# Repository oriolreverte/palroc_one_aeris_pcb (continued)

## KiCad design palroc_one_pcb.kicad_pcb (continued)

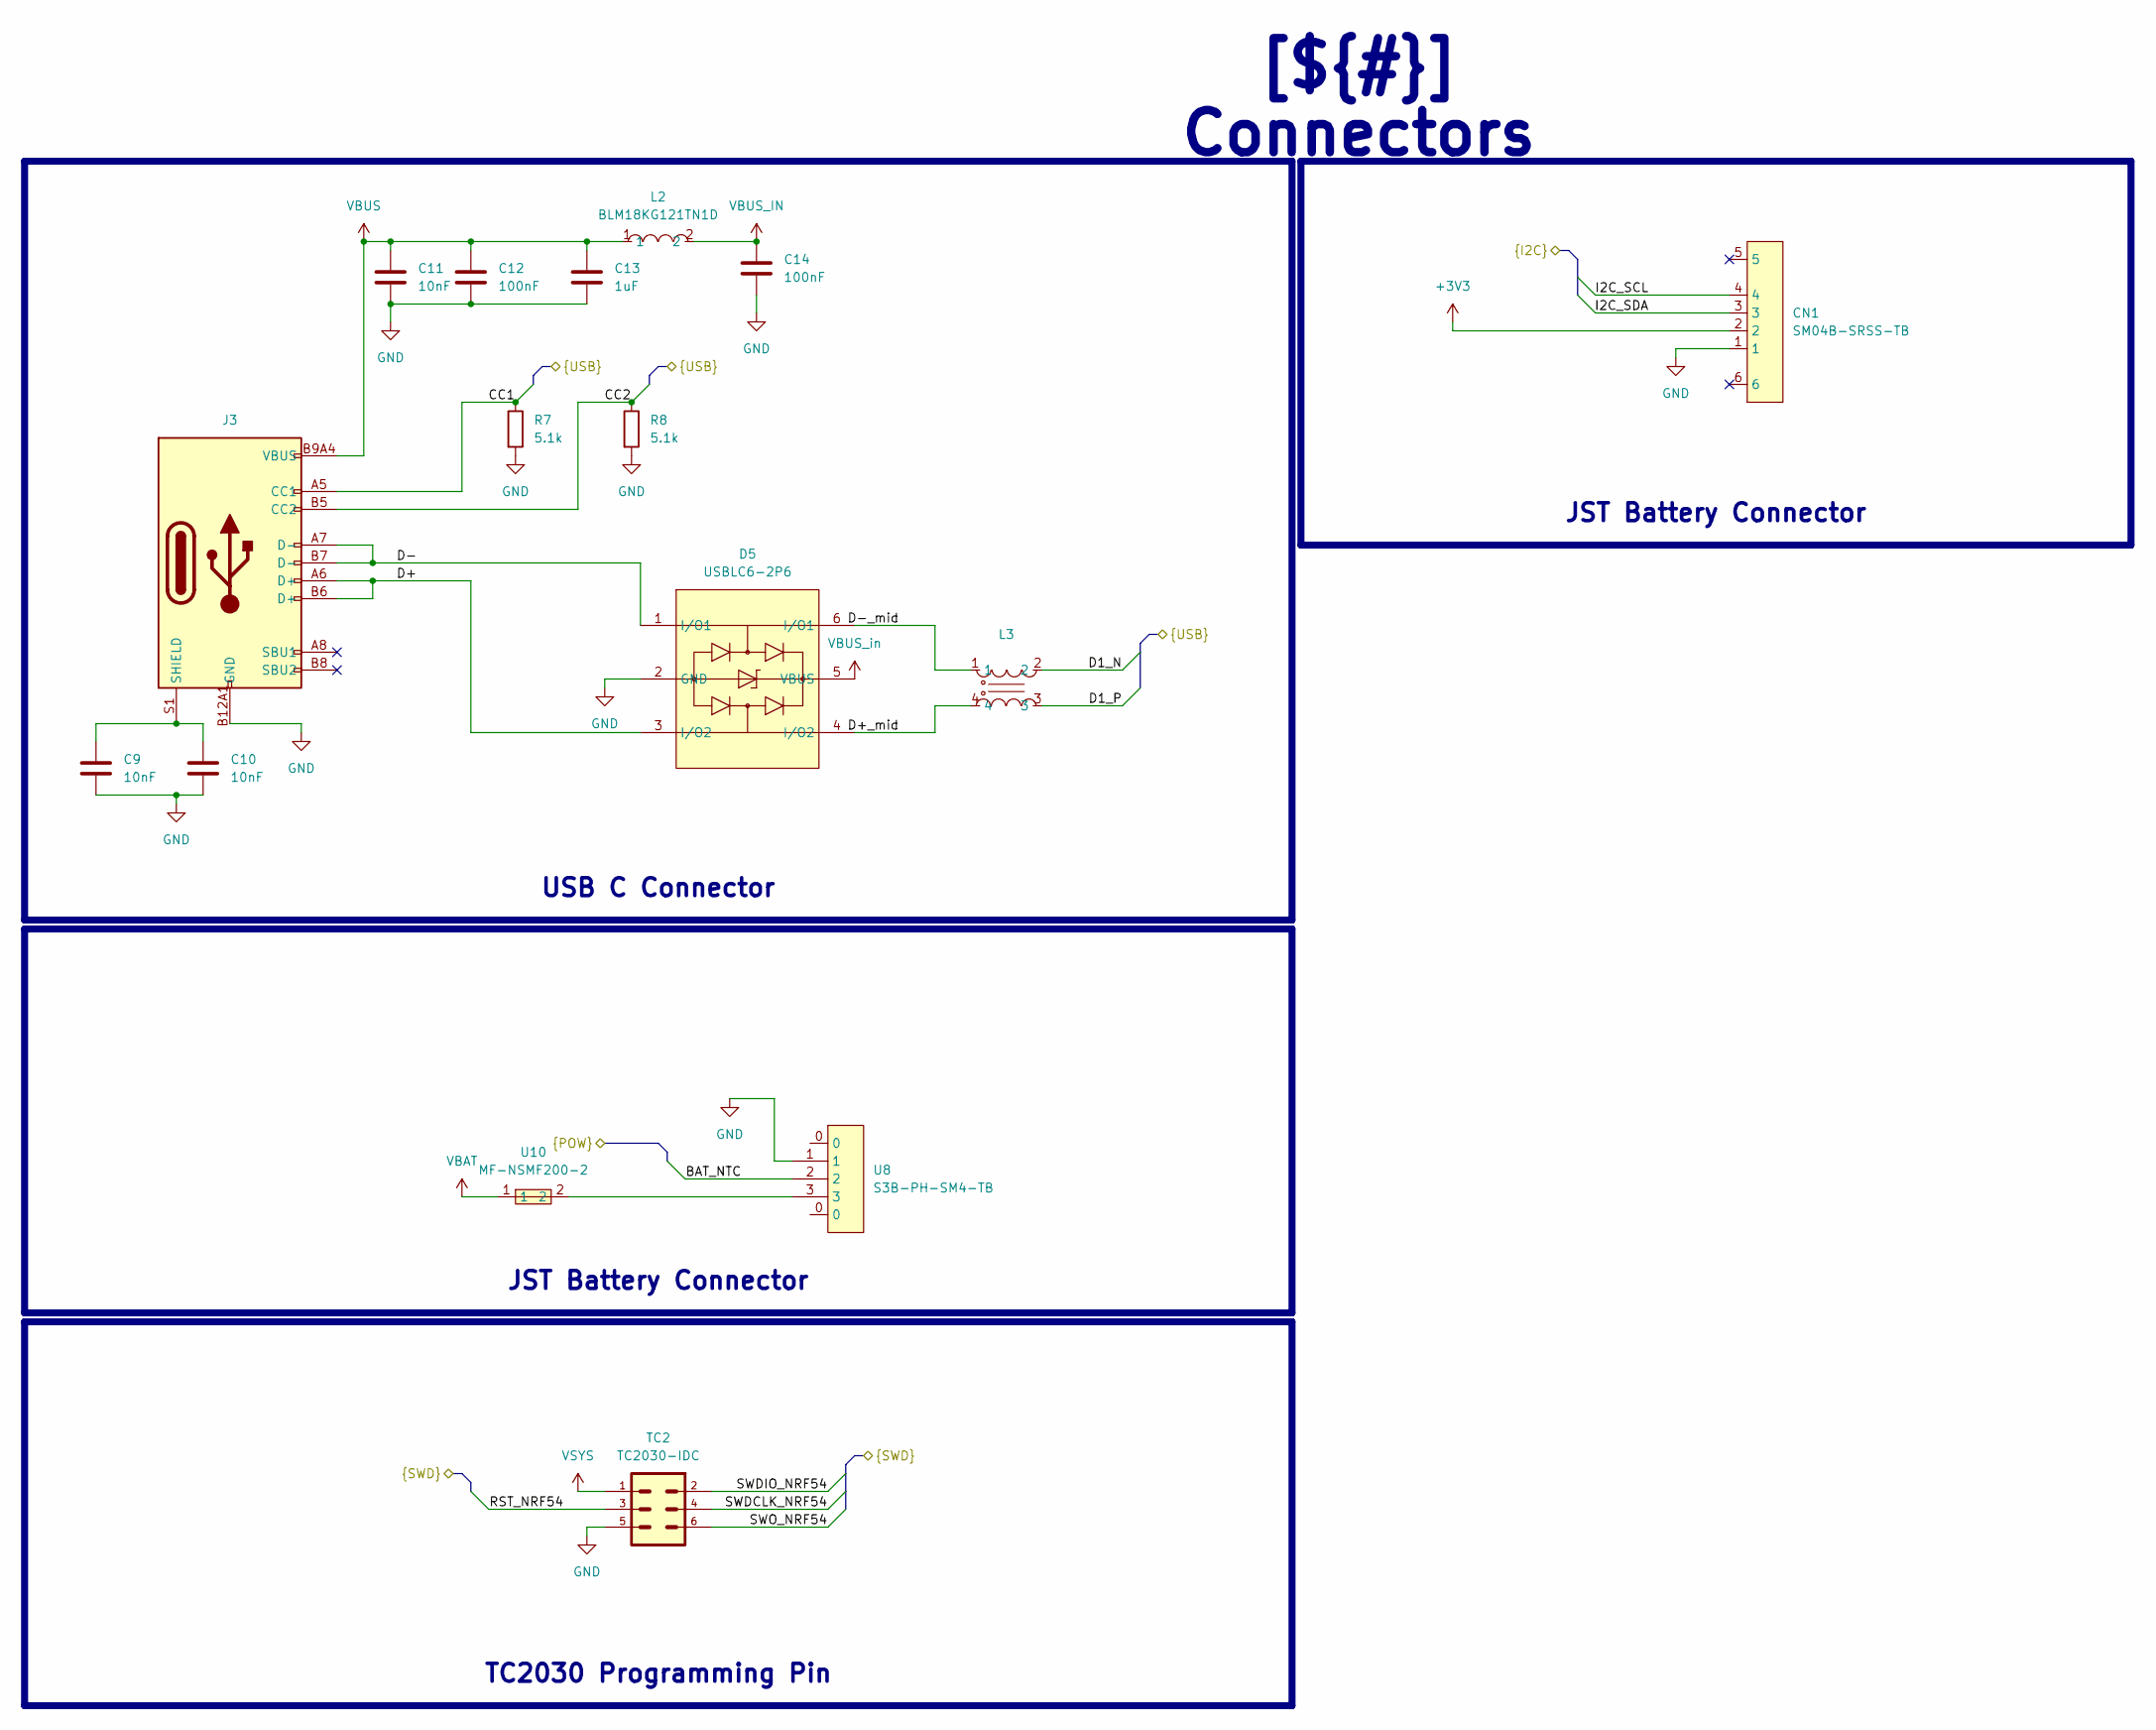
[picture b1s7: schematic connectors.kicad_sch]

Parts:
C9, C10, C11: 10nF; c_0402_nordic; LCSC C15195
C12, C14: 100nF; c_0402_nordic; LCSC C1525
C13: 1uF; c_0402_nordic; LCSC C52923
CN1: SM04B-SRSS-TB; CONN-SMD_4P-P1.00_SM04B-SRSS-TB-LF-SN; MPN SM04B-SRSS-TB(LF)(SN); LCSC Part C160404
D5: USBLC6-2P6; SOT-666-6_L1.6-W1.2-P0.50-LS1.6-BR; MPN USBLC6-2P6; LCSC Part C15999
J3: Connector, USB-TYPE-C-16P; TYPE-C-SMD_HX-TYPE-C-16PIN; LCSC C2927039
L2: BLM18KG121TN1D; L0603; MPN BLM18KG121TN1D; LCSC Part C85831
L3: DLM0NSN900HY2D; FILTER-SMD_4P-L0.9-W0.7-P0.50-BL-CW; MPN DLM0NSN900HY2D; LCSC Part C882594
R7, R8: 5.1k; r_0402_nordic; LCSC C25905
TC2: TC2030-IDC
U8: S3B-PH-SM4-TB; CONN-SMD_S3B-PH-SM4-TB-LF-SN; MPN S3B-PH-SM4-TB(LF)(SN); LCSC Part C265101
U10: MF-NSMF200-2; F1206; MPN MF-NSMF200-2; LCSC Part C89656

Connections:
+3V3: CN1.2; also elsewhere on the board
/Project Architecture/Connectors/BAT_NTC: U8.2; also elsewhere on the board
/Project Architecture/Connectors/CC1: J3.A5 (CC1), R7.1; also elsewhere on the board
/Project Architecture/Connectors/CC2: J3.B5 (CC2), R8.1; also elsewhere on the board
/Project Architecture/Connectors/D1_N: L3.2; also elsewhere on the board
/Project Architecture/Connectors/D1_P: L3.3; also elsewhere on the board
/Project Architecture/Connectors/D+: D5.3 (I/O2), J3.A6 (D+), J3.B6 (D+)
/Project Architecture/Connectors/D+_mid: D5.4 (I/O2), L3.4
/Project Architecture/Connectors/D-: D5.1 (I/O1), J3.A7 (D-), J3.B7 (D-)
/Project Architecture/Connectors/D-_mid: D5.6 (I/O1), L3.1
/Project Architecture/Connectors/I2C_SCL: CN1.4; also elsewhere on the board
/Project Architecture/Connectors/I2C_SDA: CN1.3; also elsewhere on the board
/Project Architecture/Connectors/RST_NRF54: TC2.3; also elsewhere on the board
/Project Architecture/Connectors/SWDCLK_NRF54: TC2.4; also elsewhere on the board
/Project Architecture/Connectors/SWDIO_NRF54: TC2.2; also elsewhere on the board
/Project Architecture/Connectors/SWO_NRF54: TC2.6; also elsewhere on the board
GND: C9.2, C10.2, C11.2, C12.2, C13.2, C14.2, CN1.1, D5.2 (GND), J3.A12B1 (GND), J3.B12A1 (GND), R7.2, R8.2, TC2.5, U8.1; also elsewhere on the board
unnamed: C9.1, C10.1, J3.S1 (SHIELD)
unnamed: U8.3, U10.2
VBAT: U10.1; also elsewhere on the board
VBUS: C11.1, C12.1, C13.1, J3.A9B4 (VBUS), J3.B9A4 (VBUS), L2.1
VBUS_IN: C14.1, L2.2
VBUS_in: D5.5 (VBUS); also elsewhere on the board
VSYS: TC2.1; also elsewhere on the board

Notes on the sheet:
USB C Connector
JST Battery Connector
[${#}] ${TITLE}
TC2030 Programming Pin

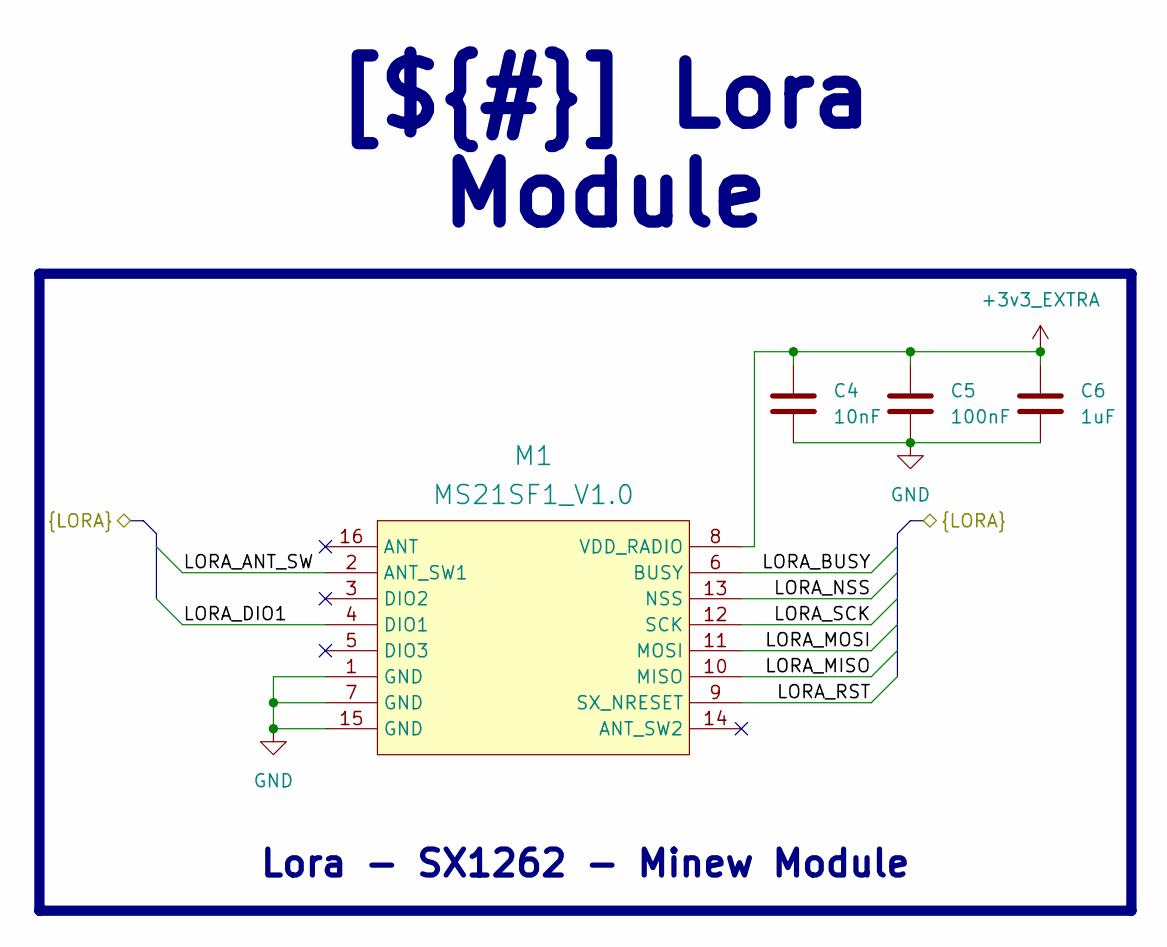
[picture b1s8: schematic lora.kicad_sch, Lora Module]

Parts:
C4: 10nF; c_0402_nordic; LCSC C15195
C5: 100nF; c_0402_nordic; LCSC C1525
C6: 1uF; c_0402_nordic; LCSC C52923
M1: MS21SF1_V1.0

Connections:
+3v3_EXTRA: C4.1, C5.1, C6.1, M1.8 (VDD_RADIO); also elsewhere on the board
/Project Architecture/LORA/LORA_ANT_SW: M1.2 (ANT_SW1); also elsewhere on the board
/Project Architecture/LORA/LORA_BUSY: M1.6 (BUSY); also elsewhere on the board
/Project Architecture/LORA/LORA_DIO1: M1.4 (DIO1); also elsewhere on the board
/Project Architecture/LORA/LORA_MISO: M1.10 (MISO); also elsewhere on the board
/Project Architecture/LORA/LORA_MOSI: M1.11 (MOSI); also elsewhere on the board
/Project Architecture/LORA/LORA_NSS: M1.13 (NSS); also elsewhere on the board
/Project Architecture/LORA/LORA_RST: M1.9 (SX_NRESET); also elsewhere on the board
/Project Architecture/LORA/LORA_SCK: M1.12 (SCK); also elsewhere on the board
GND: C4.2, C5.2, C6.2, M1.1 (GND), M1.7 (GND), M1.15 (GND); also elsewhere on the board

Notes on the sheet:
[${#}] ${TITLE}
Lora - SX1262 - Minew Module

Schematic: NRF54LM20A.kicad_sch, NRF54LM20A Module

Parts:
C1: 10nF; c_0402_nordic; LCSC C15195
C2: 100nF; c_0402_nordic; LCSC C1525
C3, C41: 1uF; c_0402_nordic; LCSC C52923
TP1: TestPoint_Probe; TestPoint_Pad_D1.0mm
U1: ME54BS13_V1.0

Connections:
+3V3: C1.1, C2.1, C3.1, U1.19 (VCC); also elsewhere on the board
/Project Architecture/Connectors/D1_N: U1.7 (D-); also elsewhere on the board
/Project Architecture/Connectors/D1_P: U1.8 (D+); also elsewhere on the board
/Project Architecture/Connectors/I2C_SCL: U1.F3 (P1.13); also elsewhere on the board
/Project Architecture/Connectors/I2C_SDA: U1.B6 (P1.07/EXTREF); also elsewhere on the board
/Project Architecture/Connectors/RST_NRF54: U1.4 (nRESET); also elsewhere on the board
/Project Architecture/Connectors/SWDCLK_NRF54: TP1.1, U1.6 (SWDCLK); also elsewhere on the board
/Project Architecture/Connectors/SWDIO_NRF54: U1.5 (SWDIO); also elsewhere on the board
/Project Architecture/Connectors/SWO_NRF54: U1.E7 (P2.09); also elsewhere on the board
/Project Architecture/DISPLAY/DISP_CS: U1.A8 (P1.04/AIN6); also elsewhere on the board
/Project Architecture/DISPLAY/DISP_DC: U1.C7 (P1.05/AIN5); also elsewhere on the board
/Project Architecture/DISPLAY/DISP_DIM: U1.E3 (P1.10); also elsewhere on the board
/Project Architecture/DISPLAY/DISP_MOSI: U1.A7 (P1.00/AIN0); also elsewhere on the board
/Project Architecture/DISPLAY/DISP_RST: U1.A6 (P1.06/AIN4); also elsewhere on the board
/Project Architecture/DISPLAY/DISP_SCK: U1.B8 (P1.03/AIN7); also elsewhere on the board
/Project Architecture/LORA/LORA_ANT_SW: U1.F5 (P1.11); also elsewhere on the board
/Project Architecture/LORA/LORA_BUSY: U1.B4 (P3.01); also elsewhere on the board
/Project Architecture/LORA/LORA_DIO1: U1.B3 (P3.02); also elsewhere on the board
/Project Architecture/LORA/LORA_MISO: U1.D5 (P3.09); also elsewhere on the board
/Project Architecture/LORA/LORA_MOSI: U1.C3 (P3.08); also elsewhere on the board
/Project Architecture/LORA/LORA_NSS: U1.D3 (P3.10); also elsewhere on the board
/Project Architecture/LORA/LORA_RST: U1.B5 (P3.00); also elsewhere on the board
/Project Architecture/LORA/LORA_SCK: U1.A3 (P3.04); also elsewhere on the board
/Project Architecture/Misc/AMP_SD: U1.C2 (P3.07); also elsewhere on the board
/Project Architecture/Misc/AUD_ENABLE: U1.B0 (P0.02); also elsewhere on the board
/Project Architecture/Misc/BTN_0: U1.12 (P1.26); also elsewhere on the board
/Project Architecture/Misc/BTN_1: U1.D6 (P1.09); also elsewhere on the board
/Project Architecture/Misc/BTN_2: U1.C6 (P1.08); also elsewhere on the board
/Project Architecture/Misc/BTN_3: U1.C0 (P0.05); also elsewhere on the board
/Project Architecture/Misc/I2S_BCLK: U1.B2 (P3.03); also elsewhere on the board
/Project Architecture/Misc/I2S_DIN: U1.C4 (P3.06); also elsewhere on the board
/Project Architecture/Misc/I2S_LRCLK: U1.C5 (P3.05); also elsewhere on the board
/Project Architecture/Misc/INT1_ACCEL: U1.F2 (P1.14); also elsewhere on the board
/Project Architecture/Misc/INT2_ACCEL: U1.F4 (P1.12); also elsewhere on the board
/Project Architecture/Misc/LED1_B: U1.F6 (P1.27); also elsewhere on the board
/Project Architecture/Misc/LED1_G: U1.E5 (P1.25); also elsewhere on the board
/Project Architecture/Misc/LED1_R: U1.E4 (P1.22); also elsewhere on the board
/Project Architecture/Misc/SPI_EXT_MEM_CS: U1.D8 (P2.05); also elsewhere on the board
/Project Architecture/Misc/SPI_MISO: U1.C8 (P2.04); also elsewhere on the board
/Project Architecture/Misc/SPI_MOSI: U1.D9 (P2.02); also elsewhere on the board
/Project Architecture/Misc/SPI_SCK: U1.E9 (P2.01); also elsewhere on the board
/Project Architecture/Misc/VIB_ENABLE: U1.E2 (P3.12); also elsewhere on the board
/Project Architecture/Misc/VIB_PWM: U1.D2 (P3.11); also elsewhere on the board
/Project Architecture/NRF54LM20A/UART_RX: U1.16 (P1.17)
/Project Architecture/NRF54LM20A/UART_TX: U1.17 (P1.16)
GND: C1.2, C2.2, C3.2, C41.2, U1.1 (GND), U1.3 (GND), U1.10 (GND), U1.11 (GND), U1.20 (GND), U1.D0 (GND), U1.E0 (GND), U1.F0 (GND); also elsewhere on the board
VBUS_out: C41.1, U1.9 (VBUS); also elsewhere on the board

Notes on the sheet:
J. Pieper ADC investigation
STM32G474 Datasheet p.81
AN5346
[${#}] ${TITLE}
Block Description

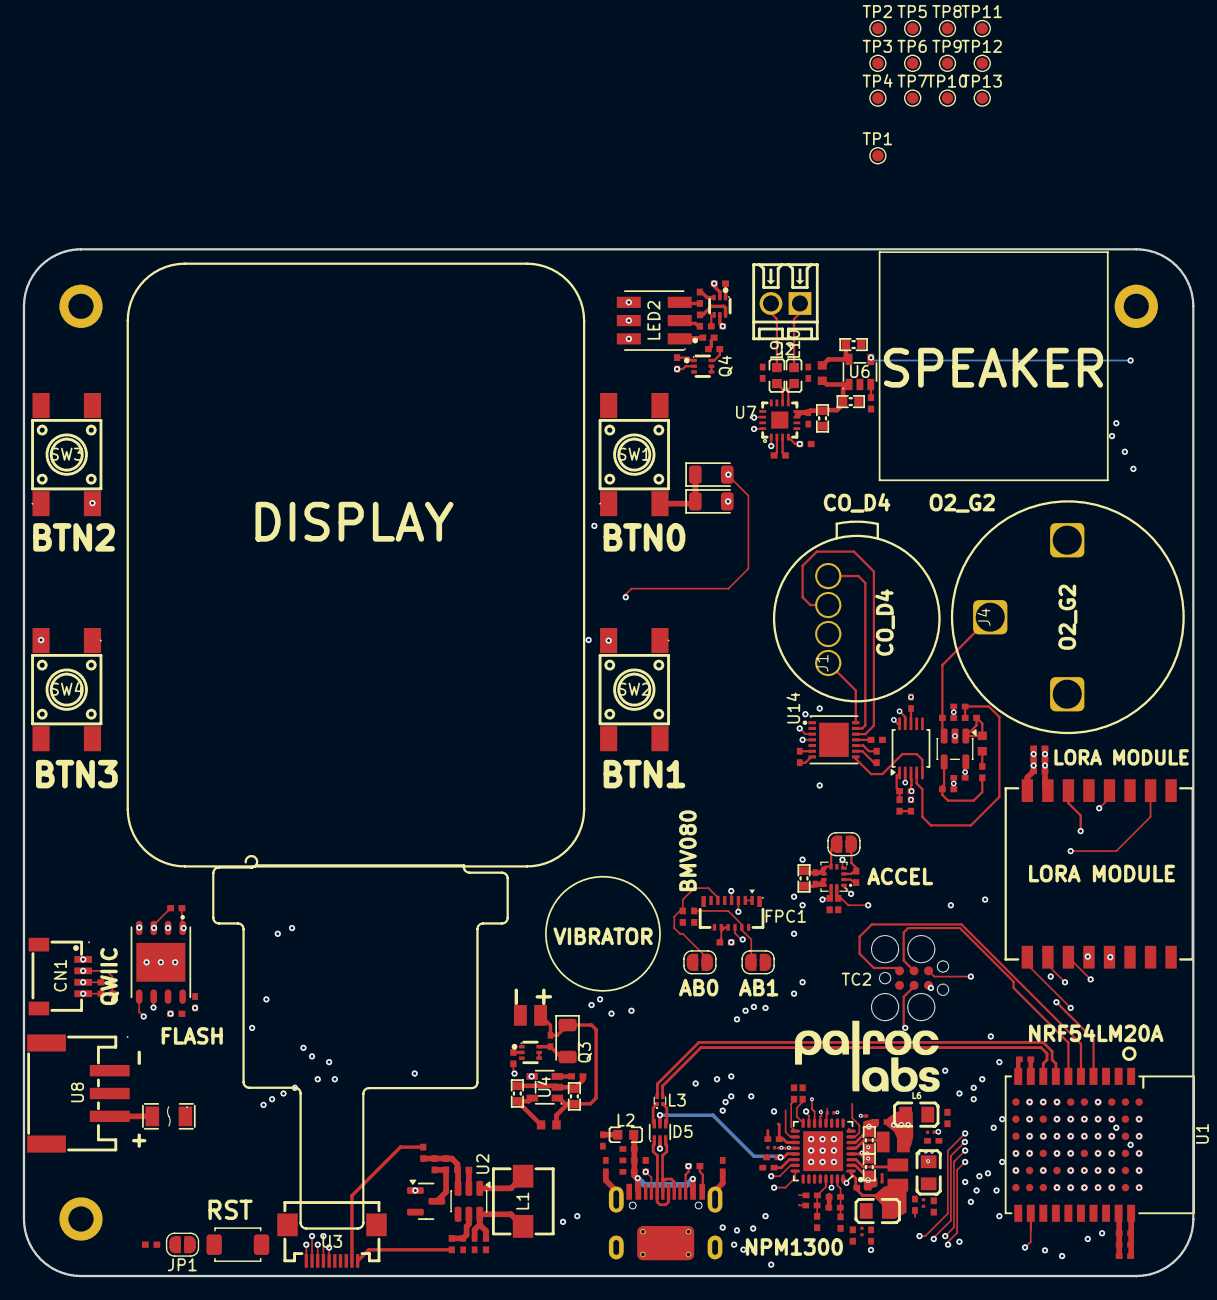
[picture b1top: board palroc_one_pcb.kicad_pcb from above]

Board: 6 copper layers, 102.5 x 90.0 mm, 171 parts (0 on the bottom side), 125 nets.

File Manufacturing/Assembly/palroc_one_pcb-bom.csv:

Row,Quantity Per PCB,References,Value,Datasheet,Footprint,Description,Manufacturer,Manufacturer Part Number,Supplier Part Number
1,3,C32 C33 C34,100pF,~,c_0201_nordic,100pF 25V C0G ±2% 0201 Multilayer Ceramic Capacitors MLCC - SMD/SMT ROHS,Murata,GRM0335C1E101GA01D,
2,3,C8 C38 C39,220pF,~,c_0402_nordic,220pF 50V X7R ±10% 0402 Multilayer Ceramic Capacitors MLCC - SMD/SMT ROHS,,,
3,3,C20 C25 C26,1nF,~,c_0201_nordic,1nF ±10% 25V Ceramic Capacitor X7R 0201,YAGEO,CC0201KRX7R8BB102,
4,5,C1 C4 C9 C10 C11,10nF,~,c_0402_nordic,10nF 50V X7R ±10% 0402 Multilayer Ceramic Capacitors MLCC - SMD/SMT ROHS,,,
5,13,C2 C5 C12 C14 C17 C37 C40 C42 C48 C49 C50 C51 C52,100nF,~,c_0402_nordic,100nF 16V X7R ±10% 0402 Multilayer Ceramic Capacitors MLCC - SMD/SMT ROHS 100nF 10V X5R ±10% 0201 MLCC - HRE,HRE,CGA0201X5R104K100ET,
6,7,C3 C6 C7 C13 C15 C35 C41,1uF,~,c_0402_nordic,1uF 25V X5R ±10% 0402 Multilayer Ceramic Capacitors MLCC - SMD/SMT ROHS 25V 1uF X5R ±10% 0402 Multilayer Ceramic Capacitors MLCC - SMD/SMT ROHS,Samsung Electro-Mechanics,CL05A105KA5NQNC,
7,1,C16,2.2uF,~,c_0402_nordic,2.2uF ±10% 16V Ceramic Capacitor X5R 0402,Samsung Electro-Mechanics,CL05A225KO5NQNC,
8,8,C18 C24 C36 C43 C44 C45 C46 C47,10uF,~,c_0603_nordic,10uF ±10% 10V Ceramic Capacitor X5R 0603 10V 10uF X5R ±10% 0603 Multilayer Ceramic Capacitors MLCC - SMD/SMT ROHS,Samsung Electro-Mechanics,CL10A106KP8NNNC,
9,9,C19 C21 C22 C23 C27 C28 C29 C30 C31,10uF,~,c_0402_nordic,10uF 10V X5R ±20% 0402 MLCC,Samsung Electro-Mechanics,CL05A106MP5NUNC,
10,9,CN1 FPC1 J1 J2 J4 S1 TC2 U3 U8,SM04B-SRSS-TB,https://lcsc.com/product-detail/Others_JST-Sales-America__JS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,CONN-SMD_4P-P1.00_SM04B-SRSS-TB-LF-SN,"Generic connector, single row, 01x04, script generated (kicad-library-utils/schlib/autogen/connector/) Generic screw terminal, single row, 01x02, script generated (kicad-library-utils/schlib/autogen/connector/) Generic connector, single row, 01x03, script generated (kicad-library-utils/schlib/autogen/connector/) Without 50mA 4mm 100MΩ 100000 Times 12V 160gf 3mm 2mm Round Button Standing paste SPST SMD Tactile Switches ROHS",JST Kyocera AVX XUNPU,,
11,3,D2 D3 D4,1N4001W,https://wmsc.lcsc.com/wmsc/upload/file/pdf/v2/lcsc/230925101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,D_SOD-123FL,Independent Type 1A 50V 1V@1.0A SOD-123FL Diodes - General Purpose ROHS,hongjiacheng,,
12,1,D5,USBLC6-2P6,https://lcsc.com/product-detail/Diodes-ESD_STMicroelectronic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,SOT-666-6_L1.6-W1.2-P0.50-LS1.6-BR,USBLC6-2P6,ST(意法半导体),,
13,1,J3,"Connector, USB-TYPE-C-16P",https://atta.szlcsc.com/upload/public/pdf/source/20220920/0E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,TYPE-C-SMD_HX-TYPE-C-16PIN,3A 1 Horizontal attachment 16P Female -25℃~+85℃ Type-C SMD USB Connectors ROHS,,,
14,2,L4 L5,2.2uH,~,l_0806_nordic,1.7A 2.2uH 2.4A 140mΩ ±20% 0806 Fixed Inductors RoHS,muRata,DFE201610E-2R2M=P2,
15,1,L2,BLM18KG121TN1D,https://lcsc.com/product-detail/Ferrite-Beads-And-Chips_muRa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,L0603,,muRata(村田),,
16,2,L9 L10,BLM18PG471SN1D,https://lcsc.com/product-detail/Ferrite-Beads-And-Chips_muRa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,L0603,,muRata(村田),,
17,3,L6 L7 L8,BLM21AG102SN1D,https://lcsc.com/product-detail/Ferrite-Beads-And-Chips_muRa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,L0805,,,,
18,1,L1,CXP0530-220M-AG(22UH),,IND-SMD_L5.7-W5.2,,,,
19,1,L3,DLM0NSN900HY2D,https://www.lcsc.com/datasheet/C882594.pdf,FILTER-SMD_4P-L0.9-W0.7-P0.50-BL-CW,,muRata(村田),,
20,1,LED2,XL-5050RGBC,https://www.lcsc.com/datasheet/C2843868.pdf,LED-ARRAY-SMD_6P-L5.0-W5.0-TL-RD_3,,XINGLIGHT(成兴光),,
21,1,M1,MS21SF1_V1.0,,MS21SF1_V1.0,PCB文件名称：MS21SF1_GBR_V1.0；PCB版本名称：MS21SF1_V1.0；单板尺寸：16.4*15.0*1.0mm；拼板要求：110.0*85.6*1.0mm，6*4 有工艺边；板厚要求：成品板外围尺寸公差:±0.1mm；板厚公差1.0±0.1mm；加工要求：4层板 板材材质 FR-4、铜厚1OZ、 黑油白字、沉金、塞孔工艺、全测；          附件50Ω阻抗图中绿框部分线路需要控制50Ω阻抗；          在每个单板PCB指定位置加入批次标注。标注字符宽度0.15mm，字符高度0.8mm，参照附件效果图；          PCB叠层按附件PCB叠层图中的指定叠层进行生产；层叠：1-  Top layer（GTL）; 2- GND（G1）; 3-POWER（G2）; 4-  Bottom layer（GBL）,,,
22,1,Q1,AO3400A,https://www.lcsc.com/datasheet/lcsc_datasheet_1811081213_Alp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,Q_SOT-23,"30V 5.7A 26.5mΩ@10V,5.7A 1.4W 1.5V@250uA 1 N-Channel SOT-23-3L MOSFETs ROHS",Alpha & Omega Semicon,,
23,3,Q3 Q4 Q5,"SSM6N56FE,LM",https://lcsc.com/product-detail/MOSFET_TOSHIBA_SSM6N56FE-LM_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,ES6_L1.6-W1.2-P0.50-LS1.6-BL,,TOSHIBA(东芝),,
24,12,R1 R3 R6 R13 R14 R15 R16 R17 R25 R33 R44 R50,0,~,r_0402_nordic,Resistor,Panasonic,ERJ-2GE0R00X,
25,2,R4 R5,10,~,r_0402_nordic,-55℃~+155℃ 10Ω 50V 62.5mW Thick Film Resistor ±1% ±200ppm/℃ 0402 Chip Resistor - Surface Mount ROHS,,,
26,1,R2,47,~,r_0402_nordic,-55℃~+155℃ 47Ω 50V 62.5mW Thick Film Resistor ±1% ±100ppm/℃ 0402 Chip Resistor - Surface Mount ROHS,,,
27,5,R28 R29 R31 R32 R45,100,~,r_0402_nordic,62.5mW Thick Film Resistors 50V ±1% ±200ppm/°C 100Ω 0402 Chip Resistor - Surface Mount ROHS,,,
28,1,R46,1k,~,r_0402_nordic,62.5mW Thick Film Resistors 50V ±100ppm/°C ±1% 1kΩ 0402 Chip Resistor - Surface Mount ROHS,,,
29,11,R7 R8 R21 R22 R30 R34 R35 R36 R40 R41 R42,5.1k,~,r_0402_nordic,-55℃~+155℃ 5.1kΩ 50V 62.5mW Thick Film Resistor ±1% ±100ppm/℃ 0402 Chip Resistor - Surface Mount ROHS,,,
30,1,R52,30k,~,r_0603_nordic,100mW Thick Film Resistors 75V ±100ppm/°C ±1% 30kΩ 0603 Chip Resistor - Surface Mount ROHS,,,
31,1,R51,47k,~,r_0402_nordic,62.5mW Thick Film Resistors 50V ±100ppm/°C ±1% 47kΩ 0402 Chip Resistor - Surface Mount ROHS,,,
32,5,R19 R23 R37 R38 R39,100k,~,r_0402_nordic,-55℃~+155℃ 100kΩ 50V 62.5mW Thick Film Resistor ±1% ±100ppm/℃ 0402 Chip Resistor - Surface Mount ROHS,,,
33,3,R10 R11 R48,300k,~,r_0402_nordic,62.5mW Thick Film Resistors 50V ±100ppm/°C ±1% 300kΩ 0402 Chip Resistor - Surface Mount ROHS,,0402WGF3003TCE,
34,5,R18 R20 R24 R26 R27,1Meg,~,r_0402_nordic,-55℃~+155℃ 1MΩ 50V 62.5mW Thick Film Resistor ±1% ±100ppm/℃ 0402 Chip Resistor - Surface Mount ROHS,,,
35,4,SW1 SW2 SW3 SW4,ZX-QC66-8.5TP,https://www.lcsc.com/datasheet/C7470159.pdf,KEY-SMD_4P-L6.0-W6.0-P4.50-LS8.6_H8.5,,Megastar(兆星),,
36,1,U5,${ALTIUM_VALUE},,Nordic_QFN50P500X500X90-33N,"Li-Ion/Li-Polymer USB-C battery charger with high efficiency buck regulators, LDOs or load switches, LED drivers, TWI and VBUSOUT",Nordic Semiconductor,nPM1300-QEAA,
37,1,U12,ADS1115IDGS,http://www.ti.com/lit/ds/symlink/ads1115.pdf,TSSOP-10_3x3mm_P0.5mm,"Ultra-Small, Low-Power, I2C-Compatible, 860-SPS, 16-Bit ADCs With Internal Reference, Oscillator, and Programmable Comparator, VSSOP-10",,,
38,1,U2,AP3019AKTR,https://www.diodes.com/assets/Datasheets/AP3019A.pdf,SOT-23-6,"1.2MHz White LED Boost Drivers with Built-in Schottky, 2.5..16Vin, <30Vout, SOT-23-6",,,
39,1,U11,LIS2DW12TR,https://lcsc.com/product-detail/Motion-Sensors-Accelerometer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,LGA-12_L2.0-W2.0-P0.50-BL,,ST(意法半导体),,
40,1,U14,LMP91000SDX/NOPB,,WSON-14_L4.0-W4.0-P0.50-BL-EP-1,,,,
41,1,U7,MAX98357AETE+T,https://www.lcsc.com/datasheet/C910544.pdf,TQFN-16_L3.0-W3.0-P0.50-BL-EP1.5,,ADI(亚德诺)/MAXIM(美信),,
42,1,U1,ME54BS13_V1.0,,ME54BS13_V1.0,ME54BS13_GBR_V1.0，ME54BS13_V1.0，16.5*12.0*1.0mm，110.0*77.5*1.0mm，7*3 有工艺边（工艺边需铺实铜），8层三阶HDI（3+2+3）板， 板材材质 FR-4，铜厚1OZ，沉金，过孔塞孔工艺，盘中孔电镀填平，绿油白字，全测,,,
43,1,U10,MF-NSMF200-2,https://lcsc.com/product-detail/Surface-Mount-Fuses_BOURNS_M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,F1206,,BOURNS,,
44,2,U4 U6,MT9700-N,https://www.lcsc.com/datasheet/C42441843.pdf,SOT-23-5_L2.9-W1.6-P0.95-LS2.9-BL,,西安航天民芯,,
45,1,U13,OPA333xxDBV,http://www.ti.com/lit/ds/symlink/opa333.pdf,SOT-23-5,"Single 1.8V, microPower, CMOS Operational Amplifiers, Zero-Drift Series, SOT-23-5",,,
46,1,U9,W25Q128JVPIQTR,https://lcsc.com/product-detail/Others_Winbond-Elec-W25Q128J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,WSON-8_L6.0-W5.0-P1.27-BL-EP,,,,
